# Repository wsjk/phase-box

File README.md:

# Phase Box 🎛️

> **RP2040-Powered Polyrhythmic Modulation Engine & MIDI Synthesizer**

Phase Box is a dedicated hardware modulation engine and MIDI generator built on the Raspberry Pi RP2040. It translates algorithmic phase accumulators, generative LFSR Turing machine registers, and polyrhythmic macro scaling into real-time MIDI Control Change (CC) streams over both **DIN/TRS 31,250 baud serial MIDI** and **class-compliant USB-MIDI**.

Designed specifically for controlling video synthesizers (such as LZX Industries, Auto Waaaves, and r_e_c_u_r), modular audio rigs, and DAWs.

*The Raylib desktop simulator (`./build-native/phase_box_native_sim`).*

---

## 📚 Documentation Quick Links

* 📖 **[User Guide & Operating Manual](docs/USER_GUIDE.md)**: Hardware controls, menu pages, tap tempo, footswitches, expression encoder, screensaver, and desktop simulator guide.
* 🛠️ **[Developer & Architecture Guide](docs/DEVELOPER_GUIDE.md)**: Dual-core architecture, signal flow diagrams, **"C++ Crash Course for Python Programmers"**, and step-by-step contribution recipes.
* 🎨 **[Raylib Desktop UI Guide](docs/RAYLIB_UI_GUIDE.md)**: Beginner-friendly guide to modifying the desktop simulator GUI, colors, controls, and Raylib primitives.
* 📐 **[Context Handover Blueprint](docs/phase_box_context_handover_blueprint.md)**: Complete implementation state and execution phases.
* 📝 **[Releases](https://github.com/wsjk/phase-box/releases)**: The changelog. Every merge to `main` is tagged and released, and the notes list the merged PRs. The version shows in the simulator's title bar and in `picotool info` for the firmware.

---

## ⚡ Key Features

- **Asymmetric Dual-Core Architecture:**
  - **Core 0 (Real-Time Control & MIDI Engine):** Quadrature decoding of both rotary encoders (value + expression), switch debouncing, 60 Hz modulation engine step, Turing LFSR mutation, bandwidth-managed MIDI CC dispatch over UART (31,250 baud on GP0) and TinyUSB USB-MIDI, and 30 FPS OLED frame rendering into lock-free shared buffers.
  - **Core 1 (Async Display & Screen Saver):** Dedicated SSD1306 128×32/64 OLED driver on `i2c0` offloading all display traffic from Core 0 via lock-free seqlock framebuffers, plus automatic screen burn-in contrast dimming.
- **Polyrhythmic Macro Engine:** Independent clock multipliers/subdivisions per CC destination (0.125× to 8×: 1/8×, 1/4×, 1/2×, 3/4×, 1×, 1.5×, 2×, 3×, 4×, 8×) for generative, non-repeating modulation patterns.
- **Expression Encoder:** A second rotary encoder sets a global depth (0.00–1.00 in 20 clicks) that scales every destination from 50% to 100%.
- **Generative Turing LFSR:** 16-bit shift register with probabilistic mutation stepped per master cycle or manual footswitch tap.
- **Performance Controls:** Freeze (expression encoder click), bypass (third footswitch), reset / undo (hold both left footswitches 2 s) and 8 preset slots (press and turn the encoder).
- **Presets in Flash:** 8 slots saved to the last 64 KB of the RP2040's flash, with 2 s auto-save, wear levelling and power-loss-safe writes.
- **Dual MIDI Output:** Hardware serial MIDI (31,250 baud on GP0) and plug-and-play USB-MIDI class compliance (TinyUSB).
- **Desktop Simulator:** Native Raylib desktop visualizer featuring a realistic stompbox enclosure UI, interactive mouse knob dragging (circular or vertical) and wheel detents, drag/scroll expression encoder with value ring, clickable footswitches (TAP, MUTATE, BYPASS), click-to-freeze expression encoder, live waveform visualizer, preset management, freeze, and bypass modes. Routes directly to macOS `CoreMIDI` (defaulting to `FRASIL FM-1` or virtual DAW port).
- **Zero-Hardware Testing:** Fully decoupled Hardware Abstraction Layer (HAL) with a GoogleTest host test suite (`tests/`, 186 unit tests across 41 test suites).

---

## 🔌 Hardware Pinout

| Peripheral | RP2040 Pin | Hardware Role |
| :--- | :--- | :--- |
| **MIDI Serial** | **GP0** (TX), **GP1** (RX) | `uart0` running at 31,250 baud (8N1). |
| **Rotary Encoder** | **GP2** (A), **GP3** (B), **GP6** (Switch) | Navigation, velocity-accelerated tuning, hold-to-save, press-and-turn for preset slot. |
| **OLED Display** | **GP4** (SDA), **GP5** (SCL) | `i2c0` at 400 kHz; 1 MHz is optional and beyond the SSD1306's rating (Address: `0x3C`, 128×32 or 128×64). |
| **Footswitch 1** | **GP10** | Tap tempo (40–300 BPM) & instant phase reset. |
| **Footswitch 2** | **GP11** | Turing shift register mutation trigger / cycle. Hold with Footswitch 1 for 2 s: reset / undo reset. |
| **Footswitch 3** | **GP12** | Bypass on / off. |
| **Expression Encoder** | **GP7** (A), **GP8** (B), **GP9** (Switch) | Global modulation depth, 20 clicks from 0.00 to 1.00. Click: freeze on / off. |
| **USB** | **USB D+ / D-** | Class-compliant TinyUSB MIDI device streaming. |

---

## 🚀 Quick Start Workflows

### 1. Build and Run the Desktop Simulator (macOS)
```bash
cmake -B build-native -S . -DCMAKE_POLICY_VERSION_MINIMUM=3.5
cmake --build build-native -j4
./build-native/phase_box_native_sim
```
*Sends MIDI straight to the hardware destination named **`FRASIL FM-1`** (change it with `PHASE_BOX_MIDI_DEST="Some Synth"`; `PHASE_BOX_MIDI_DEST=virtual` gives a virtual port for a DAW). `--list-midi` shows what CoreMIDI sees. If macOS MIDI is stuck, see `bash scripts/reset_coremidi.sh`.*

### 2. Run Host Unit Tests (GoogleTest)
```bash
cmake -S tests -B build-test -DCMAKE_POLICY_VERSION_MINIMUM=3.5
cmake --build build-test -j4
./build-test/run_host_tests
# Or helper script: ./.agents/skills/phase-box/scripts/build_host.sh
```
*(Runs all 186 tests covering DSP math, hardware abstraction layers, DeviceApp simulation, preset session persistence, SimLayout geometry, and CoreMIDI routing).*

### 3. Compile RP2040 Target Firmware (`.uf2`)
```bash
# Helper script (auto-detects SDK and toolchain):
./.agents/skills/phase-box/scripts/build_pico.sh

# Or manual execution:
export PATH="/Applications/CMake.app/Contents/bin:/Users/ww/tools/xpack-arm-none-eabi-gcc-15.2.1-1.1/bin:$PATH"
export PICO_SDK_PATH="/Users/ww/src/pico-sdk"
cmake -S firmware -B firmware/build -DPICO_SDK_PATH="$PICO_SDK_PATH"
cmake --build firmware/build -j4
```
*Drag-and-drop `firmware/build/phase_box_firmware.uf2` to your Raspberry Pi Pico in BOOTSEL mode.*

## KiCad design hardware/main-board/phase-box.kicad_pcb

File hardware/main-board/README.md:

# Phase Box main board (KiCad)

A two-layer carrier board for a Raspberry Pi Pico module, sized for a Hammond **1590BB** enclosure
(landscape, 119.5 × 94 mm). It follows the pinout in [`include/hal/pinout.hpp`](../../include/hal/pinout.hpp).

| File | What it is |
| :--- | :--- |
| `phase-box.kicad_pro` | KiCad 10 project (open this) |
| `phase-box.kicad_sch` | Schematic |
| `phase-box.kicad_pcb` | Board |
| `phase-box-schematic.pdf` | Schematic as a PDF |
| `render-top.png`, `render-bottom.png` | 3D renders of both sides |
| `fab/phase-box-gerbers.zip` | Gerbers + Excellon drill files, ready to upload to a fab |
| `fab/phase-box-bom.csv`, `fab/phase-box-pos.csv` | Bill of materials and pick-and-place positions |
| `fab/assembly-top.pdf`, `fab/assembly-bottom.pdf` | Assembly drawings (reference designators) |
| `fab/fit-check-1to1.pdf` | Board, lid outline and panel holes at 1:1 on A4, for checking the fit before ordering |

Status: the schematic passes ERC with no violations. The board is fully routed (Freerouting 2.5.0)
with GND pours on both layers, and passes DRC with no violations, no unconnected items and no
schematic parity issues. Pico GND pins 8 and 13 connect solidly to the pours instead of through
thermal spokes: on the front, signal tracks box them in, so a spoked connection would only reach a
small island of copper.

Design rules: 0.2 mm clearance, 0.25 mm signal tracks, 0.4 mm power tracks, 0.6/0.3 mm vias. Minimum
track width is 0.15 mm because the router narrows some tracks to 0.19 mm between Pico pins. Standard
2-layer fab processes (0.127 mm minimum) handle this.

## What is on the board

- **U1, Raspberry Pi Pico** (on the back of the board). BOOTSEL and the USB socket face the open lid side. The board
  is powered from the Pico's USB.
- **ENC1**: Alps EC11E encoder with push switch (value, page and save). **ENC2**: the same part
  (expression; its switch on GP9 is freeze).
- **J5, OLED**: a 0.96" 128×64 SSD1306 I²C module, soldered directly on its 4 pins (no socket, to keep it under
  the lid). Pin order **GND VCC SCL SDA**: some modules swap GND and VCC, so check yours. The firmware
  defaults to 64 rows to match.
- **MIDI out (DIN and TRS)**: a 74LVC2G34 buffers GP0 into one output per jack, so each current loop has its
  own driver. 3.3 V MIDI values: 33 Ω to the source pin, 10 Ω to the sink pin. **SW1** chooses the TRS
  standard: slider toward the "A" end = Type A (tip = sink), "B" end = Type B (tip = source).
- **Input conditioning** on every control line: 10 kΩ pull-up, series resistor and a capacitor at the GPIO.
  Encoders 10 kΩ / 10 nF (Bourns' recommended filter); switches 1 kΩ / 100 nF.
- **GP1** (MIDI in) is not connected. Adding MIDI in needs an optocoupler (6N138 or H11L1).

## Off-board parts and wiring (JST-XH connectors on the back)

| Connector | Pin 1 | Pin 2 | Pin 3 | Goes to |
| :--- | :--- | :--- | :--- | :--- |
| J1 FS1 TAP | signal | GND | | momentary SPST footswitch |
| J2 FS2 MUTATE | signal | GND | | momentary SPST footswitch |
| J6 FS3 BYPASS | signal | GND | | momentary SPST footswitch |
| J3 MIDI DIN | DIN pin 4 (source) | DIN pin 2 (shield) | DIN pin 5 (sink) | panel-mount 5-pin DIN |
| J4 MIDI TRS | tip | ring | sleeve | panel-mount 3.5 mm TRS |

The back silkscreen reads in pad order as seen from the back, where pin 1 (square pad) is on the right:
`DIN 5-2-4` and `S-R-T` above J3 and J4, and `TRS B <-> A` under SW1.

The Pico's micro-USB needs a short panel-mount USB extension, for example USB-C (panel) to micro-USB.
If you use USB-C at the panel and want to power the pedal from USB-C to USB-C chargers, the panel end
needs 5.1 kΩ CC pull-downs (cheap pigtails often leave them out). USB-A to USB-C cables work without them.

## Power and intended setup

The board is powered only through the Pico's USB (no 9 V jack). It draws roughly 40–60 mA: Pico
about 25 mA, OLED 10–20 mA, and up to about 7 mA per MIDI output while sending.

The intended rig puts a **CME H2MIDI Pro** between the Phase Box and the Raspberry Pis:

```
9 V pedalboard supply ──> H2MIDI Pro (DC in, 5.5 × 2.1 mm, centre-negative)
Phase Box USB ──────────> H2MIDI Pro USB-A host port (power + USB-MIDI)
H2MIDI Pro USB-C ───────> Raspberry Pi (USB host)
H2MIDI Pro DIN OUT ─────> Raspberry Pi with a MIDI input
Phase Box DIN/TRS out ──> optional, another device directly
```

- The H2MIDI Pro's USB-A host port supplies up to 5 V / 500 mA in total, well above what the Phase Box
  needs. Its manual says to use a self-powered hub if the devices on that port need more.
- The Phase Box firmware is a class-compliant USB-MIDI device (TinyUSB), which is what that host port
  expects.
- Avoid USB power banks as the only supply: many switch off below 50–100 mA.
- If everything always goes through the H2MIDI Pro over USB, the MIDI out parts (U2, C10, R21–R24, SW1,
  J3, J4) can be left unpopulated on the same board.
- The H2MIDI Pro's routing settings and how each Pi sees it have not been tried with this board.

## Parts list

| Ref | Value | Footprint |
| :--- | :--- | :--- |
| U1 | Raspberry Pi Pico (or Pico 2: same pinout) | Module:RaspberryPi_Pico_Common_THT |
| U2 | 74LVC2G34 | SOT-23-6 |
| ENC1, ENC2 | Alps EC11E with switch, 20 mm shaft | EC11E-Switch_Vertical_H20mm |
| SW1 | C&K JS202011CQN DPDT slide | SW_CK_JS202011CQN_DPDT_Straight |
| J1, J2, J6 | JST B2B-XH-A | 2-pin XH vertical |
| J3, J4 | JST B3B-XH-A | 3-pin XH vertical |
| J5 | (OLED module pins) | 1×4 2.54 mm |
| R1, R3, R5, R7, R9, R11, R13, R15, R17 (pull-ups) | 10k | 0805 |
| R2, R4, R8, R10 (encoder series) | 10k | 0805 |
| R6, R12, R14, R16, R18 (switch series) | 1k | 0805 |
| R19, R20 (I²C pull-ups) | 4.7k | 0805 |
| R21, R23 | 33 | 0805 |
| R22, R24 | 10 | 0805 |
| C1, C2, C4, C5 | 10nF | 0805 |
| C3, C6–C10, C12 | 100nF | 0805 |
| C11 | 10uF | 0805 |

All passives are 0805, so they can be hand-soldered. Their reference designators are on the fab layer
(F.Fab), not the silkscreen; plot F.Fab for an assembly drawing.

## Panel drilling (enclosure coordinates)

Measured from the lid's top-left corner, landscape, looking at the front:

| Feature | x (mm) | y (mm) |
| :--- | :--- | :--- |
| ENC1 shaft (value) | 92.0 | 32.0 |
| ENC2 shaft (expression) | 59.75 | 32.0 |
| FS1 TAP footswitch | 20.0 | 72.0 |
| FS2 MUTATE footswitch | 59.75 | 72.0 |
| FS3 BYPASS footswitch | 99.5 | 72.0 |
| OLED module, header row centre | 34.0 | 19.0 |

The board sits under the lid with its top side facing the lid. It is a strip across the top
(x 8–111.5, y 14–62, 103.5 × 48 mm). Its bottom edge is 10 mm above the footswitch centres, so it
clears all three footswitch bodies.

## Not verified

- **Mechanical fit.** The board stand-off height, the OLED window position (it depends on the module) and
  where the jacks go on the wall have not been checked against a real 1590BB. Print
  `fab/fit-check-1to1.pdf` at 100 % (no "fit to page"), measure its 50 mm scale bar, then lay it on the
  lid and check the holes and the board outline before ordering. The lid outline and holes are on the
  Dwgs.User layer, which is not sent to the fab. To redo the PDF:
  `kicad-cli pcb export pdf --mode-single --layers Edge.Cuts,Dwgs.User,F.Fab,F.CrtYd --ibt --black-and-white -o fab/fit-check-1to1.pdf phase-box.kicad_pcb`.
- **Nothing has been built or tested.**

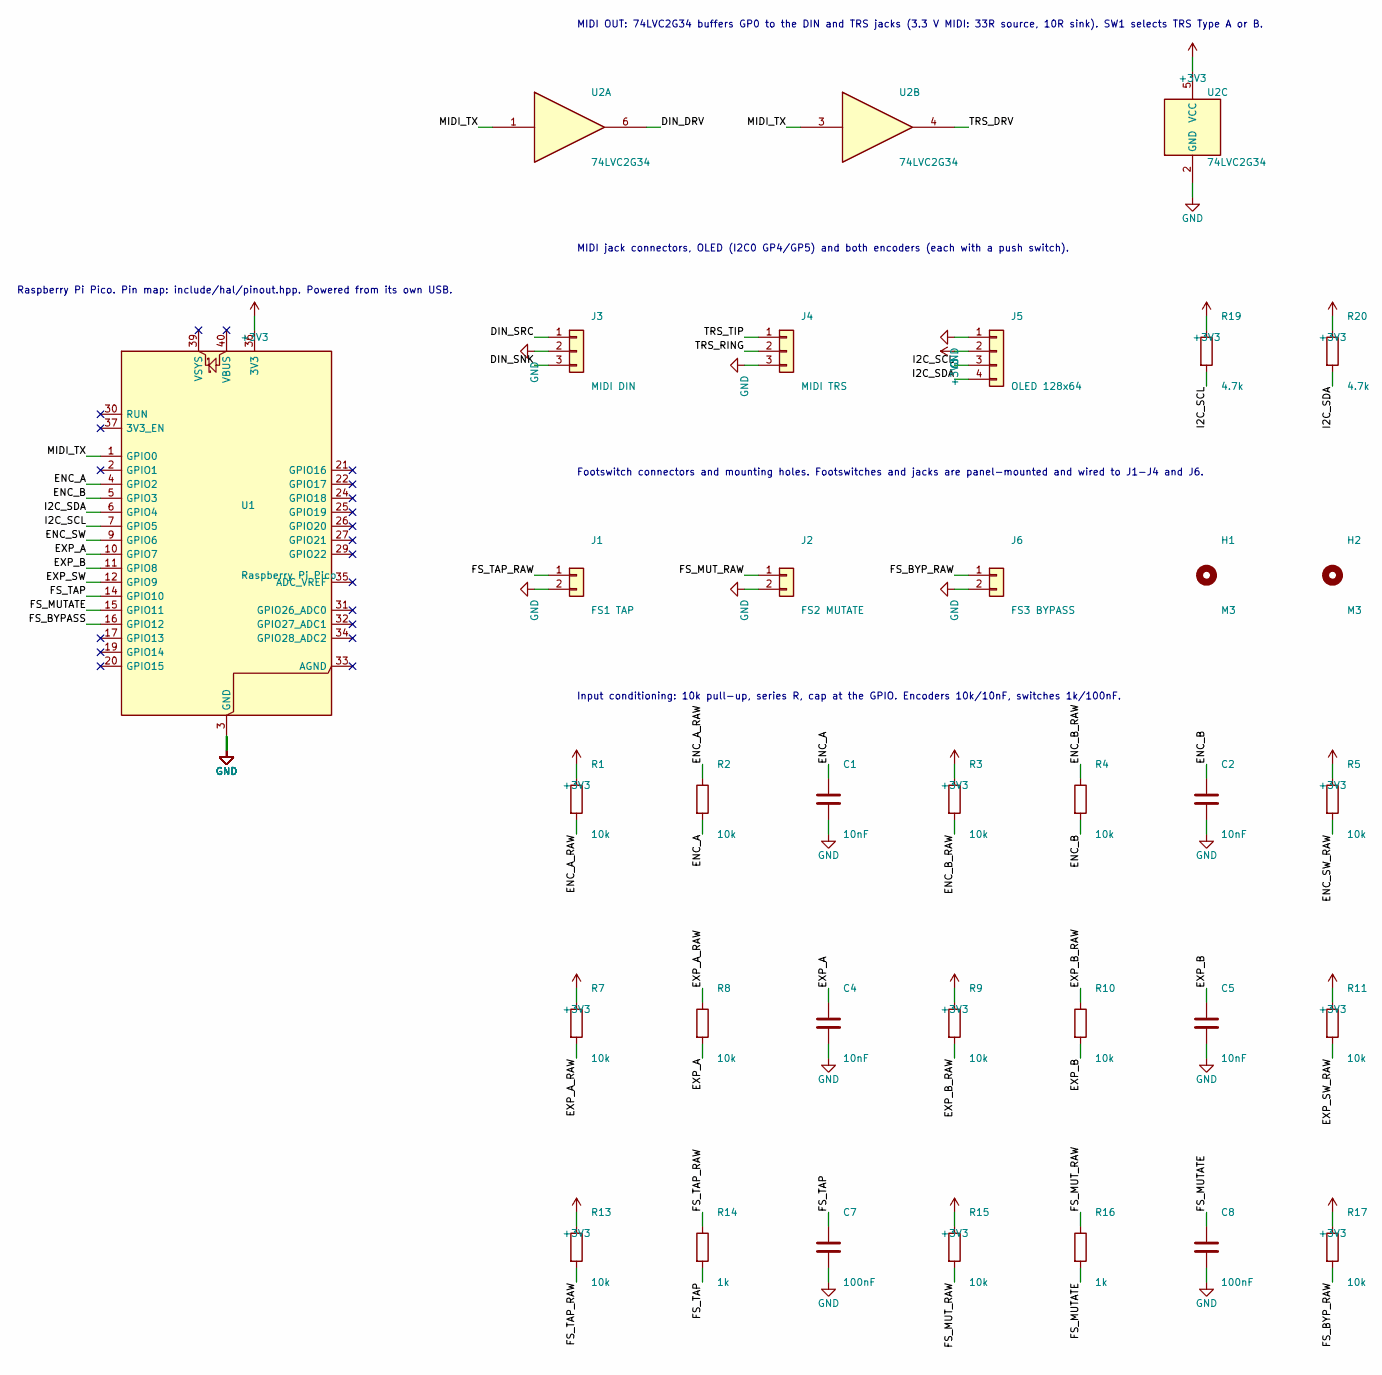
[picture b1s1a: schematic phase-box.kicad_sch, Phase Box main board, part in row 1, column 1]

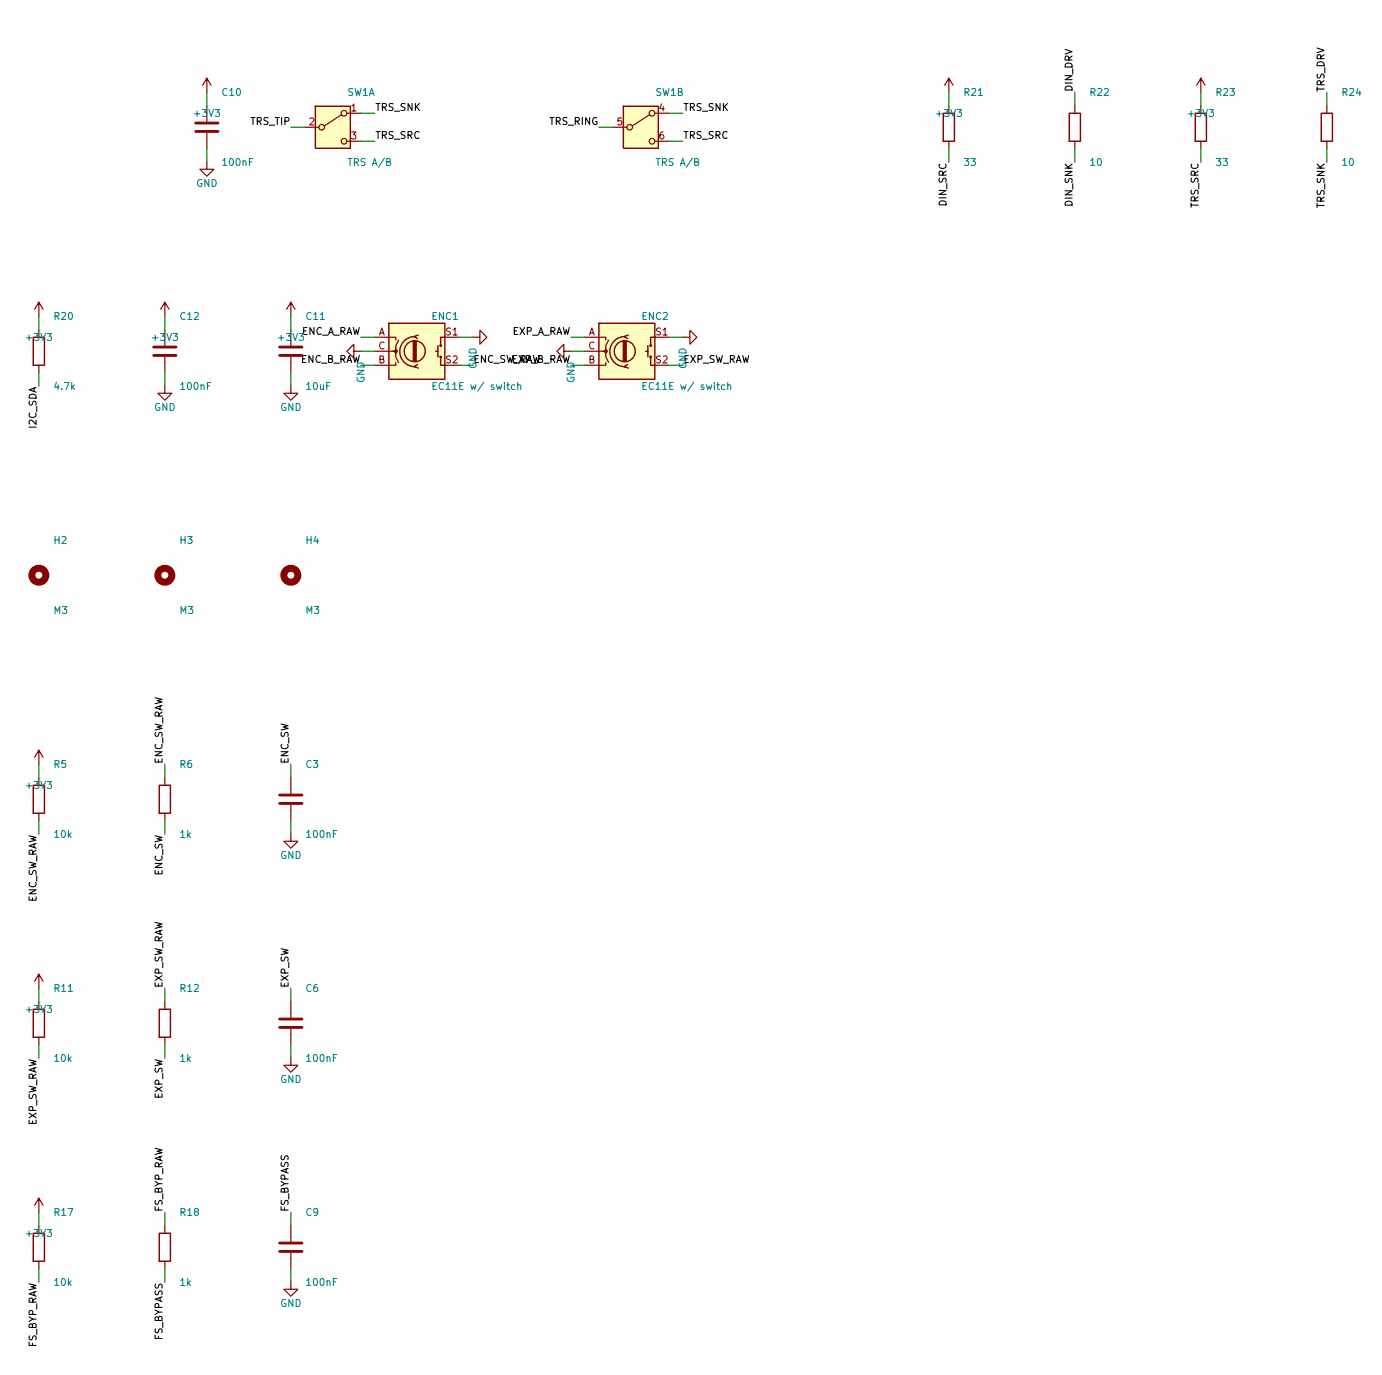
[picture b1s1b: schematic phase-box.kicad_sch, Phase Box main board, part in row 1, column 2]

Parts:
C1, C2, C4, C5: 10nF; C_0805_2012Metric
C3, C6, C7, C8, C9, C10, C12: 100nF; C_0805_2012Metric
C11: 10uF; C_0805_2012Metric
ENC1, ENC2: EC11E w/ switch; RotaryEncoder_Alps_EC11E-Switch_Vertical_H20mm
H1, H2, H3, H4: M3; MountingHole_3.2mm_M3
J1: FS1 TAP; JST_XH_B2B-XH-A_1x02_P2.50mm_Vertical
J2: FS2 MUTATE; JST_XH_B2B-XH-A_1x02_P2.50mm_Vertical
J3: MIDI DIN; JST_XH_B3B-XH-A_1x03_P2.50mm_Vertical
J4: MIDI TRS; JST_XH_B3B-XH-A_1x03_P2.50mm_Vertical
J5: OLED 128x64; PinHeader_1x04_P2.54mm_Vertical
J6: FS3 BYPASS; JST_XH_B2B-XH-A_1x02_P2.50mm_Vertical
R1, R2, R3, R4, R5, R7, R8, R9, R10, R11, R13, R15, R17: 10k; R_0805_2012Metric
R6, R12, R14, R16, R18: 1k; R_0805_2012Metric
R19, R20: 4.7k; R_0805_2012Metric
R21, R23: 33; R_0805_2012Metric
R22, R24: 10; R_0805_2012Metric
SW1: TRS A/B; SW_CK_JS202011CQN_DPDT_Straight
U1: Raspberry Pi Pico; RaspberryPi_Pico_Common_THT
U2: 74LVC2G34; SOT-23-6

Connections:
+3V3: C10.1, C11.1, C12.1, J5.2, R1.1, R3.1, R5.1, R7.1, R9.1, R11.1, R13.1, R15.1, R17.1, R19.1, R20.1, R21.1, R23.1, U1.36 (3V3), U2.5 (VCC)
/DIN_DRV: R22.1, U2.6
/DIN_SNK: J3.3, R22.2
/DIN_SRC: J3.1, R21.2
/ENC_A: C1.1, R2.2, U1.4 (GPIO2)
/ENC_A_RAW: ENC1.A, R1.2, R2.1
/ENC_B: C2.1, R4.2, U1.5 (GPIO3)
/ENC_B_RAW: ENC1.B, R3.2, R4.1
/ENC_SW: C3.1, R6.2, U1.9 (GPIO6)
/ENC_SW_RAW: ENC1.S2, R5.2, R6.1
/EXP_A: C4.1, R8.2, U1.10 (GPIO7)
/EXP_A_RAW: ENC2.A, R7.2, R8.1
/EXP_B: C5.1, R10.2, U1.11 (GPIO8)
/EXP_B_RAW: ENC2.B, R9.2, R10.1
/EXP_SW: C6.1, R12.2, U1.12 (GPIO9)
/EXP_SW_RAW: ENC2.S2, R11.2, R12.1
/FS_BYPASS: C9.1, R18.2, U1.16 (GPIO12)
/FS_BYP_RAW: J6.1, R17.2, R18.1
/FS_MUTATE: C8.1, R16.2, U1.15 (GPIO11)
/FS_MUT_RAW: J2.1, R15.2, R16.1
/FS_TAP: C7.1, R14.2, U1.14 (GPIO10)
/FS_TAP_RAW: J1.1, R13.2, R14.1
/I2C_SCL: J5.3, R19.2, U1.7 (GPIO5)
/I2C_SDA: J5.4, R20.2, U1.6 (GPIO4)
/MIDI_TX: U1.1 (GPIO0), U2.1, U2.3
/TRS_DRV: R24.1, U2.4
/TRS_RING: J4.2, SW1.5 (B)
/TRS_SNK: R24.2, SW1.1 (A), SW1.4 (A)
/TRS_SRC: R23.2, SW1.3 (C), SW1.6 (C)
/TRS_TIP: J4.1, SW1.2 (B)
GND: C1.2, C2.2, C3.2, C4.2, C5.2, C6.2, C7.2, C8.2, C9.2, C10.2, C11.2, C12.2, ENC1.C, ENC1.S1, ENC2.C, ENC2.S1, J1.2, J2.2, J3.2, J4.3, J5.1, J6.2, U1.3 (GND), U1.8 (GND), U1.13 (GND), U1.18 (GND), U1.23 (GND), U1.28 (GND), U1.38 (GND), U2.2 (GND)

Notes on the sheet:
MIDI jack connectors, OLED (I2C0 GP4/GP5) and both encoders (each with a push switch).
Raspberry Pi Pico. Pin map: include/hal/pinout.hpp. Powered from its own USB.
Input conditioning: 10k pull-up, series R, cap at the GPIO. Encoders 10k/10nF, switches 1k/100nF.
Footswitch connectors and mounting holes. Footswitches and jacks are panel-mounted and wired to J1-J4 and J6.
MIDI OUT: 74LVC2G34 buffers GP0 to the DIN and TRS jacks (3.3 V MIDI: 33R source, 10R sink). SW1 selects TRS Type A or B.

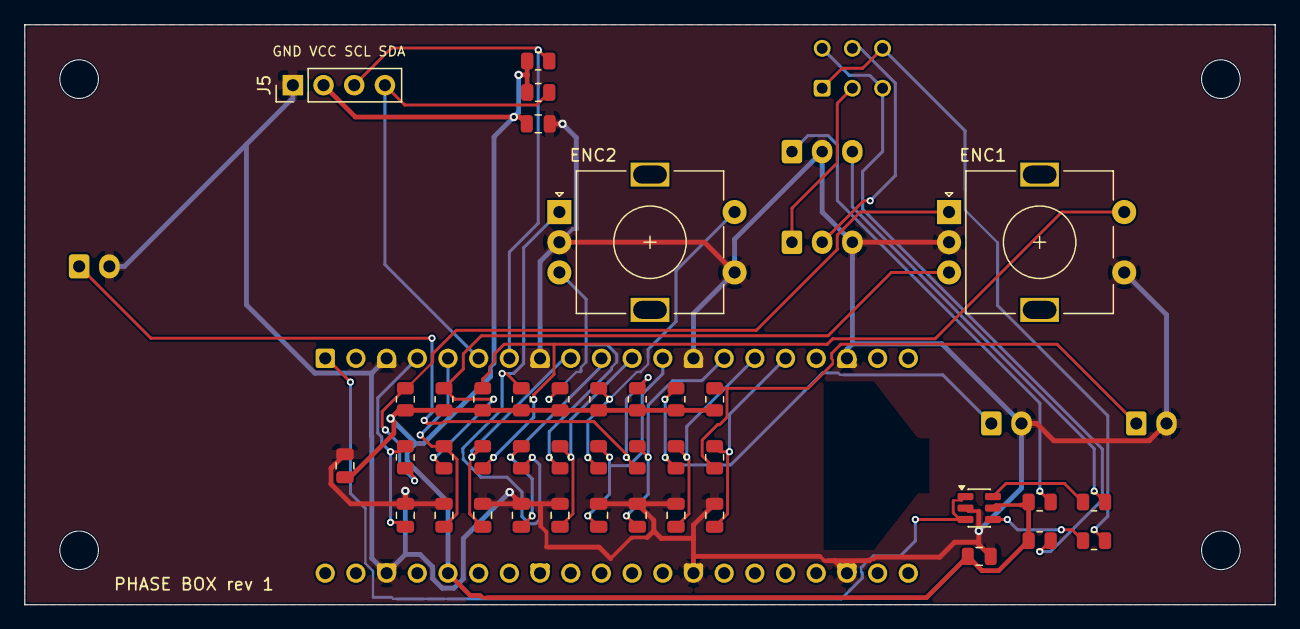
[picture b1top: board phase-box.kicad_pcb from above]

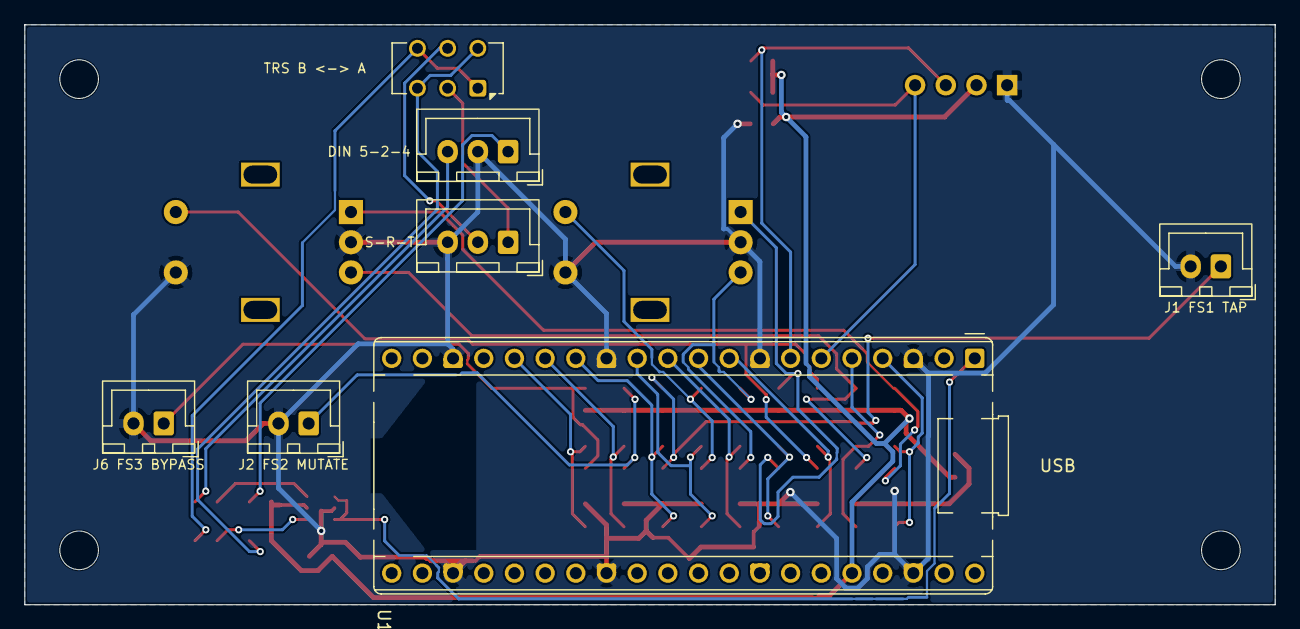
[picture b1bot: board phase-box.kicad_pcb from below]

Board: 2 copper layers, 103.5 x 48.0 mm, 51 parts (7 on the bottom side), 31 nets.

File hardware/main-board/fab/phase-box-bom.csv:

"Reference","Value","Footprint","QUANTITY"
"C1,C2,C4,C5","10nF","Capacitor_SMD:C_0805_2012Metric","4"
"C3,C6-C10,C12","100nF","Capacitor_SMD:C_0805_2012Metric","7"
"C11","10uF","Capacitor_SMD:C_0805_2012Metric","1"
"ENC1,ENC2","EC11E w/ switch","Rotary_Encoder:RotaryEncoder_Alps_EC11E-Switch_Vertical_H20mm","2"
"J1","FS1 TAP","Connector_JST:JST_XH_B2B-XH-A_1x02_P2.50mm_Vertical","1"
"J2","FS2 MUTATE","Connector_JST:JST_XH_B2B-XH-A_1x02_P2.50mm_Vertical","1"
"J3","MIDI DIN","Connector_JST:JST_XH_B3B-XH-A_1x03_P2.50mm_Vertical","1"
"J4","MIDI TRS","Connector_JST:JST_XH_B3B-XH-A_1x03_P2.50mm_Vertical","1"
"J5","OLED 128x64","Connector_PinHeader_2.54mm:PinHeader_1x04_P2.54mm_Vertical","1"
"J6","FS3 BYPASS","Connector_JST:JST_XH_B2B-XH-A_1x02_P2.50mm_Vertical","1"
"R1-R5,R7-R11,R13,R15,R17","10k","Resistor_SMD:R_0805_2012Metric","13"
"R6,R12,R14,R16,R18","1k","Resistor_SMD:R_0805_2012Metric","5"
"R19,R20","4.7k","Resistor_SMD:R_0805_2012Metric","2"
"R21,R23","33","Resistor_SMD:R_0805_2012Metric","2"
"R22,R24","10","Resistor_SMD:R_0805_2012Metric","2"
"SW1","TRS A/B","Button_Switch_THT:SW_CK_JS202011CQN_DPDT_Straight","1"
"U1","Raspberry Pi Pico","Module:RaspberryPi_Pico_Common_THT","1"
"U2","74LVC2G34","Package_TO_SOT_SMD:SOT-23-6","1"

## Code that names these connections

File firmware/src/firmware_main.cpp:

// Phase Box firmware (RP2040).
//   Core 0: USB (TinyUSB), reads the controls, runs the engine at 60 Hz, sends MIDI over USB and DIN/TRS.
//   Core 1: owns the OLED I2C bus. It only copies finished frames to the panel and dims the screen when idle.
//   Presets are saved to the last 64 KB of flash (PicoFlash + FlashPresetStorage); a save pauses both cores briefly.
// All behaviour lives in DeviceApp (include/DeviceApp.hpp), which is unit-tested on a computer; this file
// only touches pins and peripherals.
#include <atomic>
#include <cstdint>

#include "pico/stdlib.h"
#include "pico/multicore.h"
#include "hardware/gpio.h"
#include "hardware/i2c.h"
#include "bsp/board_api.h"
#include "tusb.h"

#include "DeviceApp.hpp"
#include "FlashPresetStorage.hpp"
#include "PicoFlash.hpp"
#include "PhaseBoxState.hpp"
#include "PresetManager.hpp"
#include "PresetSession.hpp"
#include "ScreenSaver.hpp"
#include "hal/pico_hal_display.hpp"
#include "hal/pico_hal_midi.hpp"
#include "hal/pinout.hpp"
#include "hal/seqlock_buffer.hpp"

// OLED rows: 64 or 32 (set with -DPHASEBOX_OLED_HEIGHT=32, or cmake -DPHASEBOX_OLED_HEIGHT=32).
#ifndef PHASEBOX_OLED_HEIGHT
#define PHASEBOX_OLED_HEIGHT 64
#endif

namespace {

constexpr uint16_t OLED_W = 128;
constexpr uint16_t OLED_H = PHASEBOX_OLED_HEIGHT;
constexpr size_t FRAME_BYTES = static_cast<size_t>(OLED_W) * OLED_H / 8;

phasebox::hal::SeqlockBuffer<FRAME_BYTES> g_shared_frame;   // Core 0 -> Core 1
std::atomic<uint32_t> g_last_activity_ms{0};                // Core 0 -> Core 1

phasebox::hal::PicoHalMidi g_uart_midi;   // uart0 on pins::UART_TX / UART_RX, 31250 baud
PhaseBoxState g_state;
PicoFlash g_flash;
FlashPresetStorage g_storage(g_flash);    // slots 1-8, kept through power-off
PresetSession g_presets(g_storage);

/// Sends every CC to the USB host (when connected) and out of the DIN/TRS jack.
class DualMidiOut : public MidiOut {
public:
    void cc(uint8_t channel, uint8_t controller, uint8_t value) override {
        if (tud_midi_mounted()) {
            uint8_t msg[3] = {static_cast<uint8_t>(0xB0 | ((channel - 1) & 0x0F)),
                              static_cast<uint8_t>(controller & 0x7F),
                              static_cast<uint8_t>(value & 0x7F)};
            tud_midi_stream_write(0, msg, 3);
        }
        g_uart_midi.send_cc(channel, controller, value);
    }
};
DualMidiOut g_midi_out;
DeviceApp g_app(g_state, g_presets, g_midi_out, OLED_W, OLED_H);

uint32_t ms_since_boot() { return to_ms_since_boot(get_absolute_time()); }

void core1_entry() {
    flash_safe_execute_core_init();   // lets Core 0 pause this core while it writes a preset to flash
    namespace pins = phasebox::hal::pins;
    phasebox::hal::PicoHalDisplay display(i2c0, pins::OLED_SDA, pins::OLED_SCL,
                                          phasebox::hal::PicoHalDisplay::DEFAULT_I2C_ADDR, OLED_W, OLED_H);
    display.init();
    display.set_contrast(ScreenSaver::CONTRAST_NORMAL);

    ScreenSaver saver;
    static uint8_t frame[FRAME_BYTES];
    uint32_t last_seq = 0xFFFFFFFFu;
    for (;;) {
        uint32_t seq;
        if (g_shared_frame.read(frame, &seq) && seq != last_seq) {   // only send frames that changed
            display.load_frame(frame, sizeof(frame));
            display.update();
            last_seq = seq;
        }
        if (saver.update(ms_since_boot(), g_last_activity_ms.load(std::memory_order_relaxed))) {
            display.set_contrast(saver.contrast());
        }
        sleep_ms(5);
    }
}

void init_input_pins() {
    namespace pins = phasebox::hal::pins;
    const unsigned list[] = {pins::ENC_A, pins::ENC_B, pins::EXP_ENC_A, pins::EXP_ENC_B, pins::ENC_SW, pins::EXP_ENC_SW,
                             pins::FS_TAP, pins::FS_MUTATE, pins::FS_BYPASS};
    for (unsigned p : list) {
        gpio_init(p);
        gpio_set_dir(p, GPIO_IN);
        gpio_pull_up(p);   // all controls switch to ground
    }
}

} // namespace

int main() {
    namespace pins = phasebox::hal::pins;

    stdio_init_all();
    board_init();
    tusb_init();

    g_uart_midi.init();
    init_input_pins();

    g_state.turing.seed(time_us_32());   // a different Turing sequence each power-up
    g_presets.load(g_state, ms_since_boot());

    multicore_launch_core1(core1_entry);

    uint64_t next_frame_us = time_us_64();

    for (;;) {
        tud_task();                                   // USB service on every pass
        const uint64_t now_us = time_us_64();

        DeviceInputs in;
        in.enc_a = gpio_get(pins::ENC_A);
        in.enc_b = gpio_get(pins::ENC_B);
        in.exp_a = gpio_get(pins::EXP_ENC_A);
        in.exp_b = gpio_get(pins::EXP_ENC_B);
        in.enc_sw = !gpio_get(pins::ENC_SW);          // active low
        in.exp_sw = !gpio_get(pins::EXP_ENC_SW);
        in.tap = !gpio_get(pins::FS_TAP);
        in.mutate = !gpio_get(pins::FS_MUTATE);
        in.bypass = !gpio_get(pins::FS_BYPASS);
        g_app.poll_inputs(in, now_us);                // as often as possible so no encoder edge is missed

        if (now_us >= next_frame_us) {
            next_frame_us += DeviceApp::FRAME_US;
            if (now_us > next_frame_us + 100000) next_frame_us = now_us + DeviceApp::FRAME_US;   // fell behind: resync
            if (g_app.frame(now_us)) g_shared_frame.write(g_app.frame_data());
            g_last_activity_ms.store(g_app.last_activity_ms(), std::memory_order_relaxed);
        }
    }
}
